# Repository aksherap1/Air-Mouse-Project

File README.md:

# Air Mouse Project

### About  
The Air Mouse is a wireless, motion-controlled computer mouse. Using an ESP32 microcontroller and an MPU-6050 IMU sensor, it detects hand movement and translates it into cursor movement on your computer. A push button allows for left-click functionality.  

This project demonstrates:

- Bluetooth HID communication
- Sensor integration
- Embedded programming w/Arduino IDE
- PCB Building
- Gyroscope + accelerometer processing
- Motion-controlled input devices
- Button input handling
- Real-time data processing
- Adjustable sensitivity & deadzone implementation

---

### Materials Used  

- ESP32 Nano Dev Board
- MPU-6050
- 4 Push Buttons
- Breadboard
- Jumper Wires
- USB Cable
- PCB

---

### Process

**1. Set up development environment**
- Install Arduino IDE
- Add ESP32 board support
- Install ESP32-BLE-Mouse library by T-vK

**2. Connect hardware (Breadboard)**
- Wire MPU-6050 to ESP32 via I2C (SDA -> ESP32 Nano D13, SCL -> ESP32 Nano D12, VCC -> 3.3V, GND -> GND)
- Connect push button to a digital input pin (e.g., D5, D6, D7, D8) & connect the other terminal to GND
- Use a breadboard for easy prototyping

**3. Test BLE Mouse**
- Open: File -> Examples ->ESP32 BLE Mouse -> BLE_Mouse in Arduino IDE
- Upload code via USB
- Check Bluetooth settings - ESP32 should appear as a mouse

**4. Integrate motion control**
- Read MPU-6050 values
- Map tilt and acceleration data to mouse movement commands
- Adjust sensitivity and filtering for smooth cursor movement

**5. Test clicking**
- Configure the push buttons to send left-click commands via BLE
- Verify clicking works with cursor movement

**6. Design a PCB**
- After a working breadboard prototype:
  - Draw schematic of ESP32, MPU-6050, and button
  - Designed PCB layout using KiCad
  - Order PCB
  - Solder components (ESP32 Nano module, sensor, button) onto the PCB
  - Upload same Arduino code to ESP32 module

7. Finalize device
- Add battery for wireless use
- Place all components in an enclosure for portability
- Ensure smooth movement and reliable clicking

---

### Analysis

- The MPU-6050 gyroscope and accelerometer detect the device's orientation and motion in 3D space. The accelerometer measures linear acceleration (tilt and movement), while the gyroscope measures rotational velocity. Together, they allow the ESP32 to move the mouse cursor based on how you tilt or rotate the device.
- Built-in gyro calibration establishes a baseline “neutral” position when the device is stationary. This means the system knows what counts as “no movement,” preventing the cursor from drifting due to small biases in the sensor readings.
- The moving average filter is a mathematical method to smooth out rapid fluctuations in sensor data. It averages several consecutive readings so that sudden spikes or jitters (like tiny hand tremors) do not cause erratic mouse movement.
- Adjustable deadzone defines a small range of tilt values that are ignored. Any motion inside this range is treated as zero, which prevents the cursor from moving unintentionally when the device is nearly still.
- Sensitivity determines how strongly tilt translates into cursor movement. Higher sensitivity makes the cursor move faster for a small tilt, while lower sensitivity requires more tilt for the same cursor motion.
- By combining calibration, filtering, deadzone, and adjustable sensitivity, the system achieves smooth, stable, and intuitive motion control, accurately translating intended device movements into cursor actions while ignoring unintended micro-movements.

---

### Citations

- https://github.com/udit1567/Circuit_forge/tree/main/Air%20Mouse
- https://github.com/T-vK/ESP32-BLE-Mouse

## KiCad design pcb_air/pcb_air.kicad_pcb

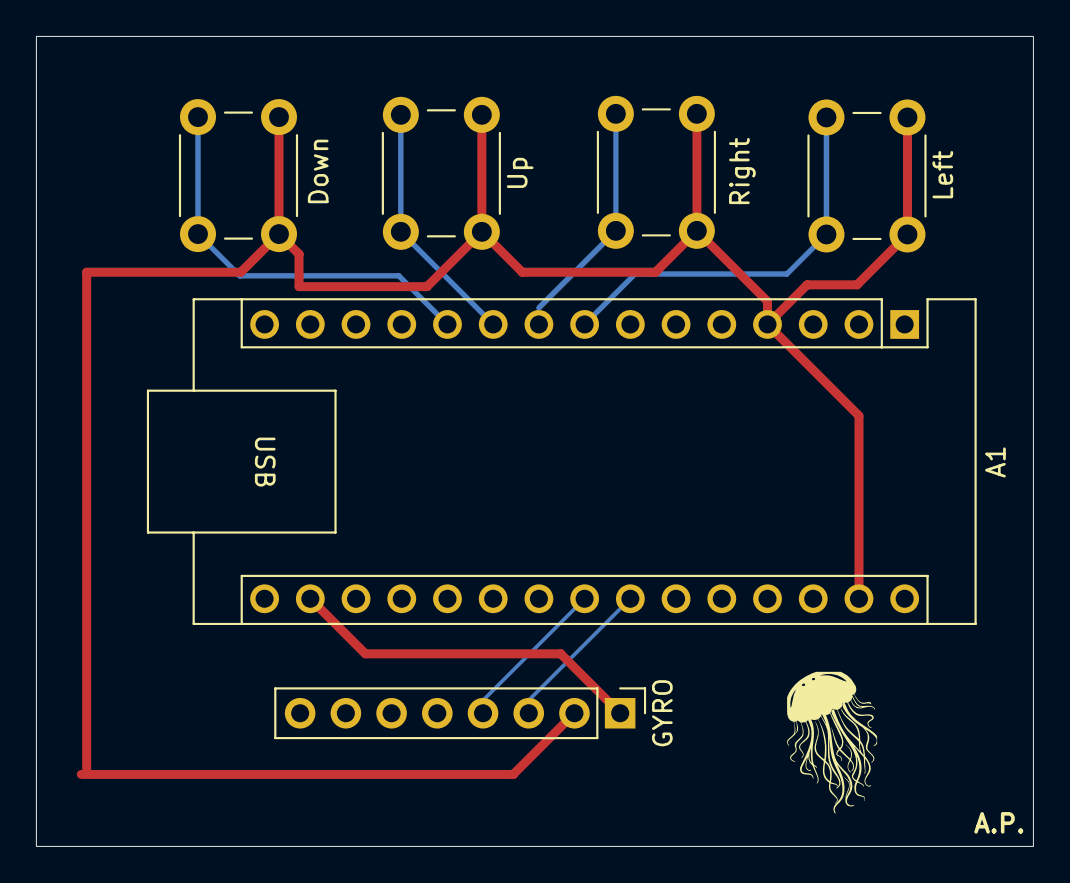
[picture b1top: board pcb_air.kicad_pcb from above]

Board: 2 copper layers, 55.4 x 45.0 mm, 6 parts (0 on the bottom side), 8 nets.

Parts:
A1: Arduino_Nano_ESP32; Arduino_Nano
Down: SW_Push; SW_PUSH_6mm
GYRO: PinHeader_1x08_P2.54mm_Vertical
Left: SW_Push; SW_PUSH_6mm
Right: SW_Push; SW_PUSH_6mm
Up: SW_Push; SW_PUSH_6mm

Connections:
+3.3V: A1.17 (3V3), GYRO.1 (VCC)
GND: A1.4 (GND), A1.29 (GND), Down.1, GYRO.2 (GND), Left.1, Right.1, Up.1
unnamed: A1.8 (D5), Left.2
unnamed: A1.9 (D6), Right.2
unnamed: A1.10 (D7), Up.2
unnamed: A1.11 (D8), Down.2
unnamed: A1.24 (SCL/A5), GYRO.3 (SCL)
unnamed: A1.23 (SDA/A4), GYRO.4 (SDA)

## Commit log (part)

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2026-01-02 Gitpush
2026-01-02 air mouse code
2026-01-03 Air mouse
